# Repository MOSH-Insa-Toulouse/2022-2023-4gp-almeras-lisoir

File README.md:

# Projet Capteur 4A Génie Physique - Nina Alméras & Emma Lisoir

## Sommaire
* [1. Description du projet](#PremiereSection)
  * [1.1. Caractéristiques et travaux de recherche préliminaires sur le capteur](#PremiereSection1)
  * [1.2. Cours et formation](#PremiereSection2)
* [2. Livrables](#DeuxiemeSection)
  * [2.1. Livrables initiaux](#DeuxiemeSection1)
  * [2.2. Révisions des livrables du projet](#DeuxiemeSection2)
* [3. Carte Arduino UNO et code associé](#TroisiemeSection)
* [4. KiCad](#QuatriemeSection)
  * [4.1. Symboles et empreintes des composants](#QuatriemeSection1)
  * [4.2. Schématique](#QuatriemeSection2)
  * [4.3. Placement des composants](#QuatriemeSection3)
  * [4.4. Visualisation 3D](#QuatriemeSection4)
* [5. Fabrication du shield](#CinquiemeSection)
  * [5.1. Réalisation du PCB](#CinquiemeSection1)
  * [5.2. Perçage et soudure](#CinquiemeSection2)
* [6. Logiciel de simulation LTSpice](#SixiemeSection)
* [7. Développement de l'interface en Python](#SeptiemeSection)
* [8. Tests et résultats](#HuitiemeSection)
  * [8.1. Banc de test](#HuitiemeSection1)
  * [8.2. Résultats obtenus et analyses](#HuitiemeSection2)
  * [8.3. Regard critique sur les résultats](#HuitiemeSection3)
* [9. Datasheet](#NeuvièmeSection)

## 1. Description du projet 

Ce projet s'inscrit dans le cadre de l'unité de formation "Du capteur au banc de test en open source hardware". Ce cours est dispensé en quatrième année au sein du département de Génie Physique de l'INSA Toulouse.
Ce projet s'étend sur le deuxième semestre de l'année 2022-2023 et a pour but de nous sensibiliser aux différentes étapes de conception et d'analyse utiles à la création d'un capteur.

### 1.1 Caractéristiques et travaux de recherche préliminaires sur le capteur 

Le KTY2000 est un exemple de technologie low-tech à base de graphite. Ce projet s’inspire du travail mené par plusieurs scientifiques et publié dans [cet article](https://www.nature.com/articles/srep03812) en 2014. En effet, les études ont révélé les nombreux avantages du carbone graphite. L’électronique à base de papier attire de plus en plus les ingénieur.es de par sa facilité d’approvisionnement, de fabrication et son faible coût. Il suffit dans notre cas de déposer une fine couche de graphite sur le substrat naturellement poreux pour former la base du capteur. Les mines de crayon sont constituées de réseaux percolés de fines poudres de graphite liées entre elles par des argiles, permettant d’obtenir après dépôt de fins films conducteurs non fabriqués en laboratoire. 

Le système à l’étude est granulaire, autrement dit il existe une dépendance entre la conductivité électrique et l’espace moyen entre les nanoparticules de graphite. Ainsi, une déformation de la feuille de papier va modifier la conductivité globale de la couche de graphite, induisant des changements de résistances réversibles lors des déformations en compression ou en traction. Ceci constitue en fait le principe d'une jauge de contrainte. 
L’expérience est réalisée avec différentes duretés de mine de crayon (2H, HB, 2B). Les mesures de résistance pour chaque crayon sont réalisées en fonction de différents rayons de courbure (soit la déformation) ou de l’angle de flexion de notre capteur. Cela permet une caractérisation complète de chaque type de crayon et ainsi de notre capteur. 

Dans notre cas, les traces de crayon sont déposées sur du papier comme vu ci-dessous. Une fois colorié, le capteur est connecté à un système de mesures externe via des pinces crocodiles reliées à un PCB et branché sur une carte Arduino Uno.

<p align="center">

### 1.2 Cours et formation 

Pour mener ce projet, nous avons d'abord suivi différents cours et TPs.
- Introduction à la chaîne de mesure
- TP développement d'un capteur à jauge de contrainte à base de crayon graphite
- TP conception d'un circuit analogique pour interfacer le capteur à jauge de contrainte
- TP programmation de microcontrôleurs et développement d'un matériel open source
- TP LTSpice afin de simuler le fonctionnement du circuit électronique comprenant la jauge de contrainte
- TP shield électronique PCB dédié à l'interface du capteur de contrainte
- TP réalisation du banc de test de la jauge de contrainte
- Cours fiche technique de la jauge de contrainte
- Cours Github

<p align="center">

## 2. Livrables du projet 

### 2.1 Livrables initiaux 

* Un shield PCB devra être designé et fabriqué. Il sera ensuite connecté à une plaque Arduino UNO. Le shield doit contenir au minimum un amplificateur transimpédence, un module Bluetooth, et si possible un écran OLED et un encodeur rotatoire pour la calibration du capteur.

* La carte Arduino fonctionnera avec un code permettant de mesurer la containte appliquée sur le capteur. Si besoin, la carte devra aussi contrôler le module Bluetooth, l'écran OLED et l'encodeur rotatoire.

* Une application Android APK
* Un protocole de test
* La datasheet du capteur de contrainte

### 2.2 Révisions des livrables du projet 
 
Notre binôme ne possède aucun téléphone Android et il n'était donc pas possible de créer une application APK et de transmettre les données par Bluetooth. Nous avons dû rediscuter les livrables avec nos responsables de projet. Finalement, nous développons une interface en Python et le module Bluetooth est supprimé. En effet, le code python créé permet la réception des données envoyées par la carte Arduino Uno, via une communication USB entre un ordinateur et la carte (port série). L'interface, confectionnée avec Qtdesigner, permet également la calibration du capteur graphite et respecte les livrables initiaux concernant l'affichage des valeurs (relatives ou non) de résistance de nos deux capteurs présents sur le setup : le KTY2000 et un flex-sensor de chez Spectral Symbol. Ce dernier est un capteur ayant les mêmes fonctionnalités que notre capteur graphite. Lorsque le flex-sensor est plié, sa variation de résistance suit la contrainte de flexion. De plus, un écran OLED affichera en temps réel de la résistance du capteur KTY2000 et celle du flex-sensor.

## 3. Carte Arduino UNO et code associé 

Le code Arduino est consultable [ici](https://github.com/MOSH-Insa-Toulouse/2022-2023-4gp-almeras-lisoir/tree/main/Arduino).
Ce code permet la réception des mesures faites par les deux capteurs, la conversion résistance-angle du flex-sensor et celle tension-résistance pour le KTY2000, la gestion de l'affichage sur l'écran OLED et l'envoi de données via un port série.

## 4. KiCad 

Voici la liste des différents composants présents sur notre PCB :

- _x2 résistance 100kΩ_
- _x2 résistance 10kΩ_
- _x2 résistance 1kΩ_
- _x1 capacité 1μF_
- _x2 capacité 100nF_
- _x1 amplificateur opérationnel LTC1050_
- _x1 écran OLED I2C 0.91_

### 4.1. Symboles et empreintes des composants 
 
* Amplificateur LTC1050
* Ecran OLED
* Flex sensor

### 4.2. Schématique 
 
<p align="center">

* Amplificateur LTC1050

* Ecran OLED

* Flex sensor

### 4.3. Placement des composants 
 
<p align="center">
 
### 4.4. Visualisation 3D 
 
<p align="center">

## 5. Fabrication du shield 
 
### 5.1 Réalisation du PCB 

Le PCB a été fabriqué grâce au matériel mis à disposition au Génie Physique et au Génie Électrique et Informatique de l'INSA Toulouse. Les manipulations ont été faites avec l'aide de Catherine Crouzet. La modélisation du PCB fait sur [KiCad](https://github.com/MOSH-Insa-Toulouse/2022-2023-4gp-almeras-lisoir/tree/main/KiCad) a été imprimée sur du papier calque tranparent. Ce motif a été ensuite transféré par UVs sur la plaquette d'epoxy finement recouverte d'une couche de cuivre. À l'aide d'un révelateur, la partie non insolée de la résine a été retirée. La plaquette d'expoxy a été ensuite placée dans un bain de perchlorure de fer pour que le cuivre non protégé par la résine soit retiré de la plaquette. Enfin, la plaque a été nettoyée des dernières traces de résine avec de l'acétone.

### 5.2 Perçage et soudure 
 
<p align="center">

⌀ 0.8mm : AOP LTC1050, résistances et capacités

⌀ 1.0mm : Broches de connexion de la carte Arduino Uno

## 6. Logiciel de simulation LTSpice 
 
L'ensemble de notre circuit électronique a été simulé sur le logiciel LTSpice afin de comprendre et d'analyser son comportement dans des conditions réelles de valeurs de tension. Les différentes simulations ont permis d'une part de vérifier le bon fonctionnement du circuit et de chacun des composants intégrés, et d'autre part de comprendre l'utilité de chacun. Les images ci-dessous représentent la schématique du circuit ainsi qu'une réponse dans le temps de notre capteur à une stimulation. Se référer à la [datasheet](https://github.com/MOSH-Insa-Toulouse/2022-2023-4gp-almeras-lisoir/blob/main/Datasheet/Datasheet%20KTY2000.pdf) pour de plus amples informations.
 
<p align="center">
<p align="center">

## 7. Développement de l'interface en Python 
 
L'interface développée répond à plusieurs problématiques et présente différentes fonctionnalités.
- Connexion automatique au port utilisé par la connexion avec l'Arduino (message pop-up selon le succès de la connection au port)
- Étape préliminaire de calibration du capteur graphite pour l'obtension de son angle de flexion
- Relecture et affichage en temps réel des données reçues pour les deux capteurs après traitement (résistance, variation relative et angle de flexion)
- Affichage de deux graphiques défilant exprimant la variation de la résistance du flex-sensor et du capteur graphite
- Fermeture de la fenêtre et interruption de la communication avec le bouton Quit

L'apparence de l'interface a été faite avec Qt Designer. Cet outil permet de créer une interface utilisateur "what-you-see-is-what-you-get" (WYSIWYG), ce qui permet un gain de temps et d'efficacité. 
Le programme Python et le fichier Qt designer sont consultables [ici](https://github.com/MOSH-Insa-Toulouse/2022-2023-4gp-almeras-lisoir/tree/main/Interface%20Python).

<p align="center">
 
Il est à noter que pour gérer à la fois la réception de données en continu et l’affichage du graphique déroulant, nous avons mis en place un thread dans notre programme Python. Le multithreading permet à un système d'exploitation la mise en place de plusieurs tâches qui fonctionnent en même temps.

## 8. Tests et résultats 

Voici le setup d'utilisation du KTY2000.
<p align="center">

### 8.1 Banc de test 
 
Pour caractériser notre capteur, nous relevons la variation (relative ou non) de résistance de notre capteur en fonction de l'angle de flexion et de la déformation du capteur. Nous avons construit un banc de test avec l'aide de disques de papier cartonné de différents rayons de courbure, visibles ci-dessous. Les mesures ont été réalisées pour une déformation en traction et en compression, le tout en utilisant des crayons graphite de différentes duretés : 2B, HB et 2H.
<p align="center">
 
### 8.2 Résultats obtenus et analyses 
Les résultats de mesure sont consultables [ici](https://github.com/MOSH-Insa-Toulouse/2022-2023-4gp-almeras-lisoir/blob/main/Datasheet/Relev%C3%A9%20de%20mesures.xlsx).

Les deux graphes suivant représentent la variation de la résistance relative (en %) en fonction de la déformation appliquée - compression et traction.
<p align="center">
<p align="center">
 
Les mines les plus tendres contiennent une proportion plus élevée de particules de graphite. C’est donc pour cette raison que les traces de ce type de crayon paraissent plus foncées sur le papier. À l’inverse, les mines les plus dures contiennent beaucoup de liants argileux et apparaissent plus claires. Cela explique également que les résistances de mines de crayon les plus tendres sont plus faibles que les mines de crayon les plus dures. En effet, sous la traction, les particules de graphite sont davantage écartées les unes des autres favorisant la déconnexion des voies de conduction : le courant est donc minime, la résistance quant à elle augmente.  Sous compression, les particules de graphite contenues dans la trace de crayon se rapprochent, facilitant la conduction du courant à travers le réseau de percolation : la résistance s’abaisse naturellement.

Cette caractéristique est illustrée à travers la variation relative de résistance en fonction de la déformation du capteur. En effet, un crayon qui contient moins de particules de graphite comme le 2H dépose naturellement moins de graphite sur le substrat. Les variations de résistance sont donc plus significatives comme beaucoup de chemins de percolations sont créés ou rompus contrairement au 2B où les déformations n’induisent que de faibles variations relatives de résistance.
 
Il est également notable que le comportement en compression du flex-sensor se rapproche de celui du KTY2000. Nous pouvons en conclure que notre capteur graphite présente des similarités de fonctionnnement qu'un capteur industriel. **Cela confirme l'idée que le low-tech est une alternative pertinente pour le futur de l'industrie.**

### 8.3 Regard critique sur les résultats 
 
Il est important de souligner la variabilité des conditions expérimentales. Entre chaque relevé de points et malgré le fait que les pinces crocodiles sans dents étaient bien fixées, il se peut que l’attache du capteur ait bougée. Les résultats sont imprécis et pour certains discutables au vu de la qualité du montage mais suivent tout de même les lois physiques. 

Nous pourrions amener plusieurs pistes d'améliorations à notre projet :

- Améliorer notre banc de test afin de garantir des résultats optimaux mais surtout pour augmenter sa durée de vie et sa résistance. Par exemple, nous pourrions concevoir de le fabriquer par l'intermédiaire d'une imprimante 3D. 

- Améliorer notre PCB en y ajoutant un potentiomètre digital à la place de R2 afin de travailler sur une plus grande gamme de résistance. La tension de sortie serait ainsi modulée en fonction de la valeur de la résistance variable. 

- Améliorer le setup expérimental en commençant par l'ergonomie de notre PCB afin de le rendre plus fonctionnel pour la réalisation des mesures de résistance. Penser à un meilleur emplacement pour les différents composants, à un système d'accroche pour l'écran OLED, mais aussi pour les pinces crocodile dans le but de limiter le plus possible la variabilité des conditions expérimentales. 

## 9. Datasheet 
 
La datasheet du KTY2000 est consultable [ici](https://github.com/MOSH-Insa-Toulouse/2022-2023-4gp-almeras-lisoir/blob/main/Datasheet/Datasheet%20KTY2000.pdf). Elle reprend tous les concepts physiques ainsi que les résultats de mesures et leur analyse. D'autres courbes illustrant la variation de résistance en fonction de l'angle de flexion y figurent, venant compléter les affirmations énoncées tout au long de ce rendu.

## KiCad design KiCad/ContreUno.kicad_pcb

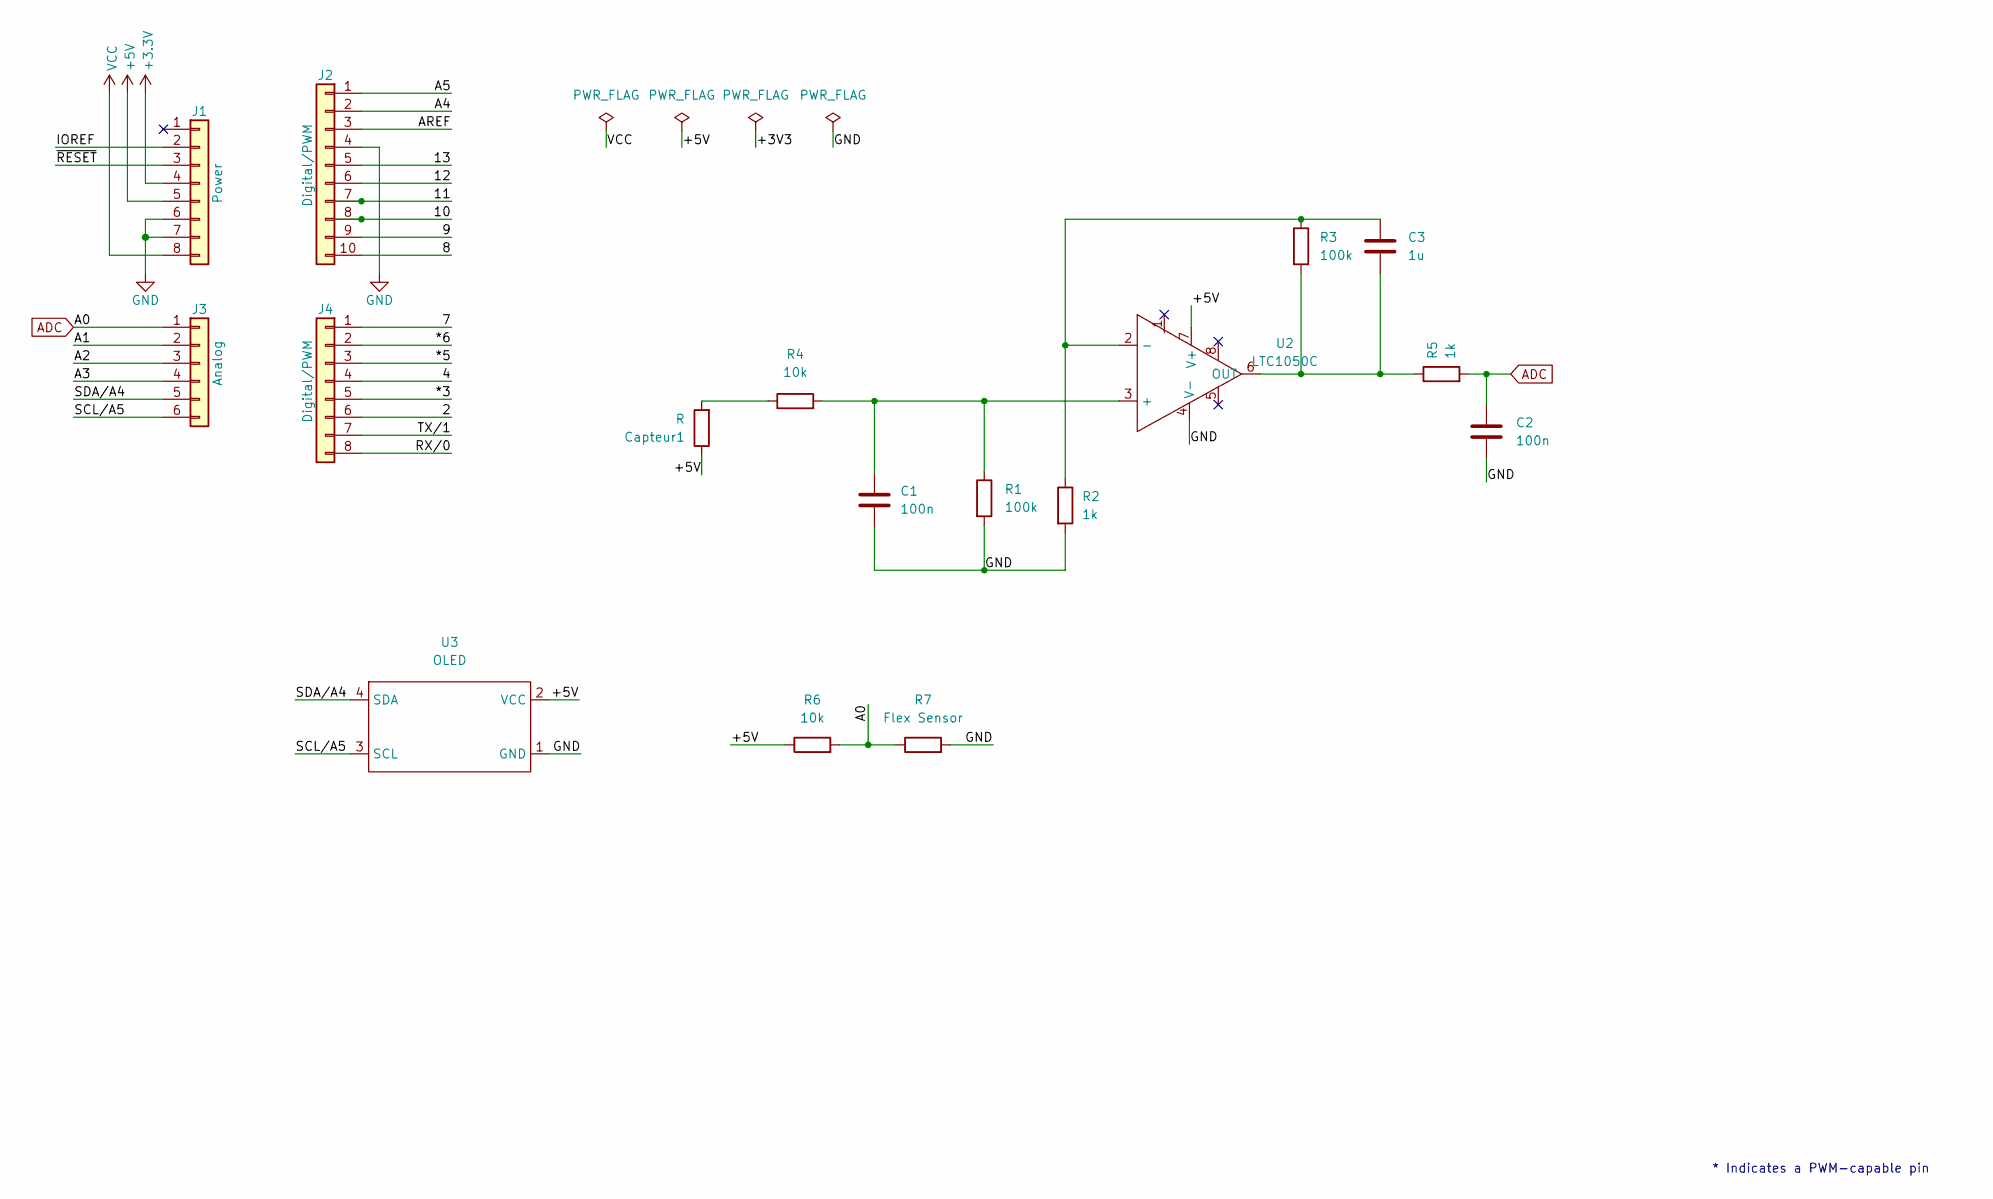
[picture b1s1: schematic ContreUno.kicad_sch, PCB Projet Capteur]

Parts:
C1, C2: 100n; C_Disc_D3.0mm_W1.6mm_P2.50mm
C3: 1u; C_Rect_L7.0mm_W4.5mm_P5.00mm
Capteur1: R; R_Axial_DIN0204_L3.6mm_D1.6mm_P5.08mm_Horizontal
J1: Power; PinSocket_1x08_P2.54mm_Vertical
J2: Digital/PWM; PinSocket_1x10_P2.54mm_Vertical
J3: Analog; PinSocket_1x06_P2.54mm_Vertical
J4: Digital/PWM; PinSocket_1x08_P2.54mm_Vertical
R1, R3: 100k; R_Axial_DIN0204_L3.6mm_D1.6mm_P5.08mm_Horizontal
R2, R5: 1k; R_Axial_DIN0204_L3.6mm_D1.6mm_P5.08mm_Horizontal
R4, R6: 10k; R_Axial_DIN0204_L3.6mm_D1.6mm_P5.08mm_Horizontal
R7: Flex Sensor; R_Axial_DIN0207_L6.3mm_D2.5mm_P2.54mm_Vertical
U2: LTC1050C
U3: OLED

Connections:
+3V3: J1.4
+5V: Capteur1.1, J1.5, R6.1, U2.7 (V+), U3.2 (VCC)
/2: J4.6
/4: J4.4
/7: J4.1
/8: J2.10
/9: J2.9
/10: J2.8
/11: J2.7
/12: J2.6
/13: J2.5
/*3: J4.5
/*5: J4.3
/*6: J4.2
/A1: J3.2
/A2: J3.3
/A3: J3.4
/A4: J2.2
/A5: J2.1
/AREF: J2.3
/IOREF: J1.2
/RX/0: J4.8
/SCL/A5: J3.6, U3.3 (SCL)
/SDA/A4: J3.5, U3.4 (SDA)
/TX/1: J4.7
/~RESET: J1.3
ADC: C2.1, J3.1, R5.2, R6.2, R7.1
GND: C1.2, C2.2, J1.6, J1.7, J2.4, R1.2, R2.2, R7.2, U2.4 (V-), U3.1 (GND)
unnamed: C1.1, R1.1, R4.2, U2.3 (+)
unnamed: C3.1, R2.1, R3.1, U2.2 (-)
unnamed: C3.2, R3.2, R5.1, U2.6 (OUT)
unnamed: Capteur1.2, R4.1
VCC: J1.8

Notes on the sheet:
* Indicates a PWM-capable pin

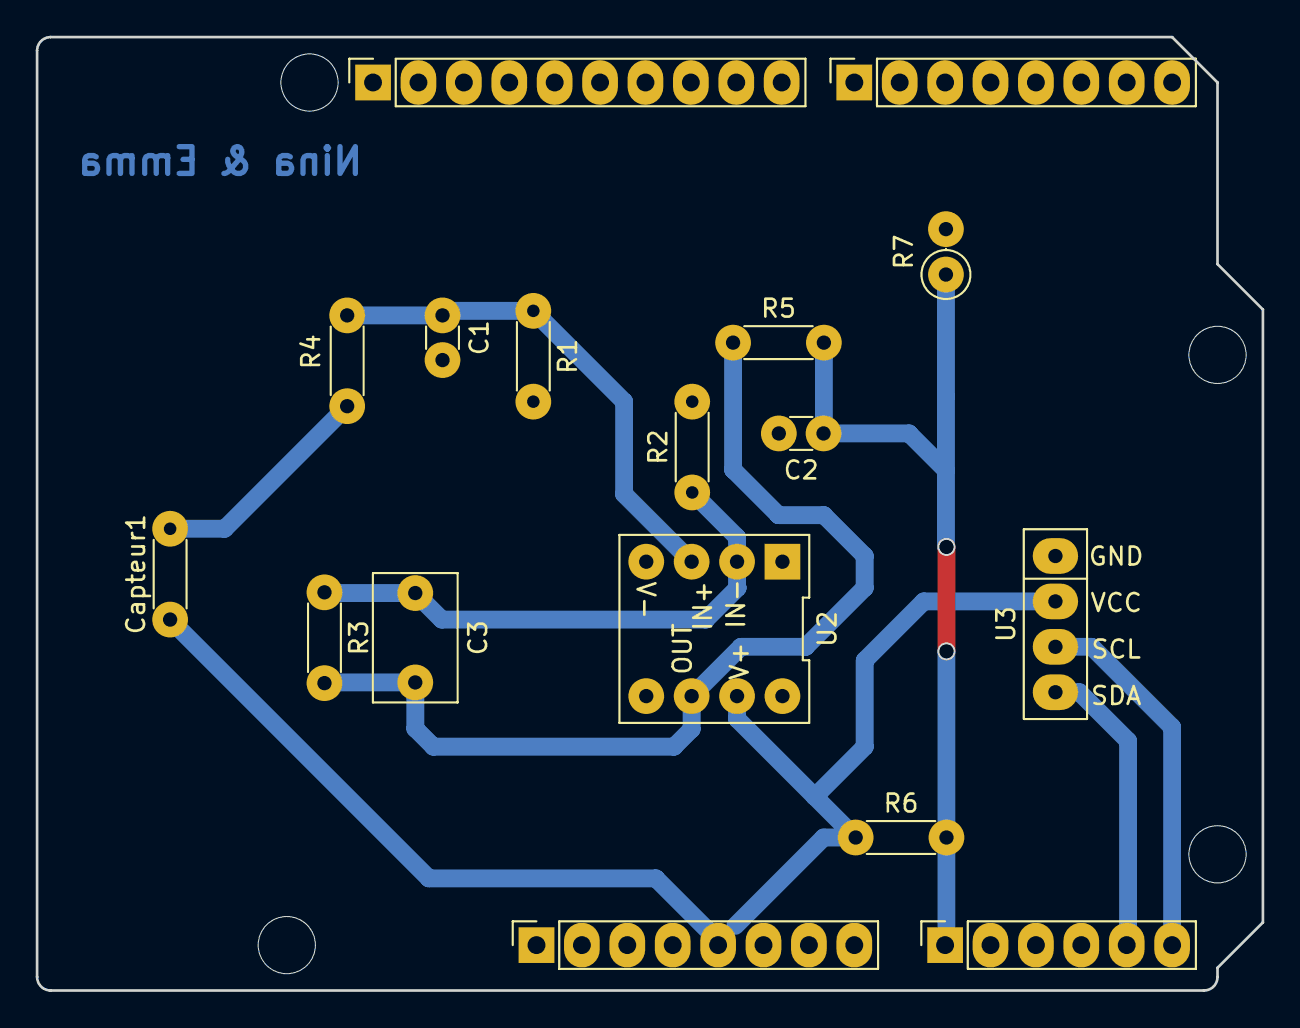
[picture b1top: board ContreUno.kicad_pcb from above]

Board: 2 copper layers, 68.6 x 53.3 mm, 21 parts (0 on the bottom side), 9 nets.

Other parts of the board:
MH1, MH2, MH3, MH4: MountingHole_3.2mm

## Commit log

2023-02-01 "Ajout TODO list"
2023-02-01 Ajout CheckBoxes
2023-02-01 checkkk
2023-04-18 Create oui bonjour
2023-04-18 Create test
2023-04-26 Create KiCad
2023-04-27 Create fp-info-cache
2023-04-27 Create fp-lib-table
2023-04-27 Create sym-lib-table
2023-04-27 Rename Arduino_MountingHole.pretty/MountingHole_1.2mm.kicad_mod to KiCad/Arduino_MountingHole.pretty/MountingHole_1.2mm.kicad_mod
2023-04-27 Rename Arduino_MountingHole.pretty/MountingHole_3.2mm.kicad_mod to KiCad/Arduino_MountingHole.pretty/MountingHole_3.2mm.kicad_mod
2023-05-01 Create Datasheet
